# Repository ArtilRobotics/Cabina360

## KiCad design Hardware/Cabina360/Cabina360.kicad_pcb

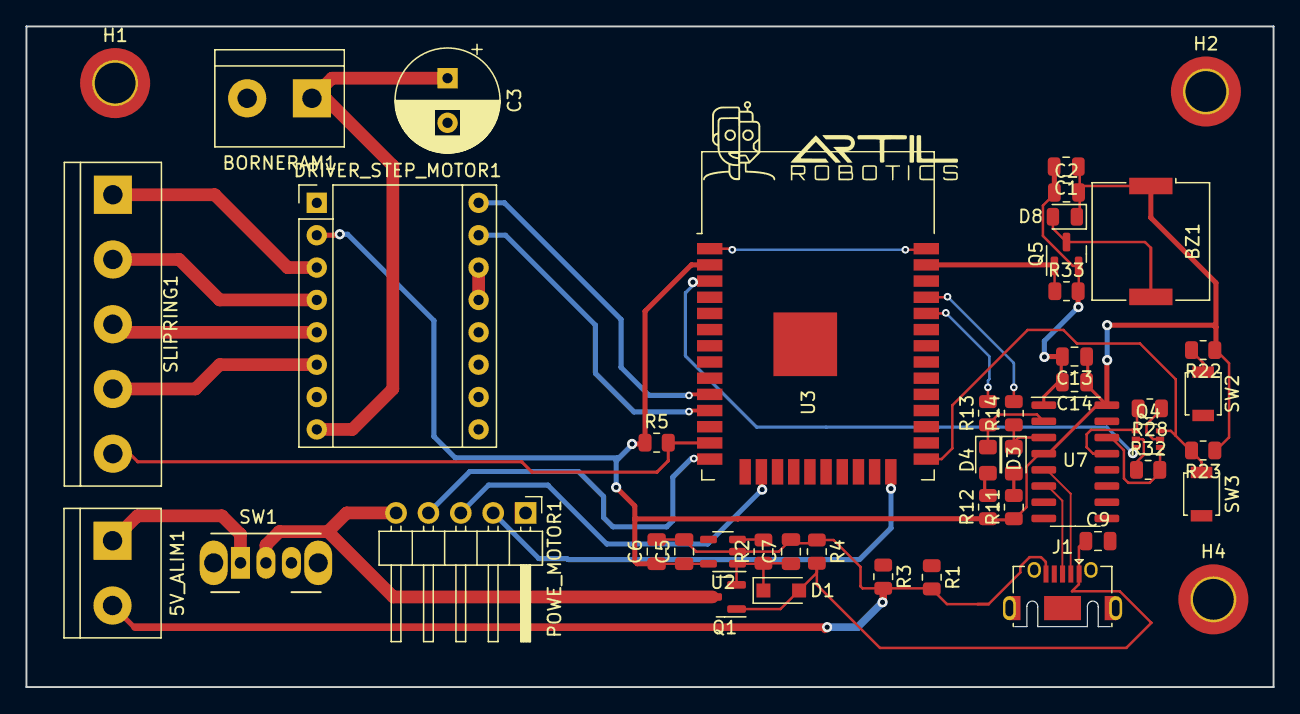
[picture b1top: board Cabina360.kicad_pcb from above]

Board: 2 copper layers, 97.9 x 51.8 mm, 46 parts (0 on the bottom side), 34 nets.

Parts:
5V_ALIM1: 5V GND; TerminalBlock_bornier-2_P5.08mm
BORNERAM1: MOTOR+ MOTOR-; TerminalBlock_bornier-2_P5.08mm
BZ1: Buzzer; Buzzer_Murata_PKMCS0909E
C1, C6, C7, C9, C13: 10uF; C_0805_2012Metric
C2: 0.1uF; C_0805_2012Metric
C3: 10uF; CP_Radial_D8.0mm_P3.50mm
C5: 1uF; C_0805_2012Metric
C14: 10nF; C_0805_2012Metric
D1: MBR1020VL; D_SOD-123F
D3, D4: LED; LED_0805_2012Metric_Pad1.15x1.40mm_HandSolder
D8: 1N4151; D_0805_2012Metric
DRIVER_STEP_MOTOR1: Pololu_Breakout_A4988; Pololu_Breakout-16_15.2x20.3mm
H1, H2, H4: MountingHole; MountingHole_3.2mm_M3_ISO14580_Pad_TopBottom
J1: USB_C_Receptacle_USB2.0; USB_Micro-AB_Molex_47590-0001
POWE_MOTOR1: PINES; PinHeader_1x05_P2.54mm_Horizontal
Q1: DMG2301L; SOT-23
Q4: MBT3904DW1; SOT-363_SC-70-6
Q5: DMG3406L; SOT-23
R1, R3: 5.1K; R_0805_2012Metric
R2, R5, R22, R23: 10K; R_0805_2012Metric
R4, R33: 100K; R_0805_2012Metric
R11, R12, R28, R32: 1K; R_0805_2012Metric
R13, R14: 100; R_0805_2012Metric
SLIPRING1: PINES; TerminalBlock_bornier-5_P5.08mm
SW1: SW_DPDT_x2; SW_CuK_OS102011MA1QN1_SPDT_Angled
SW2: Reset; SW_SPST_B3U-1000P
SW3: Boot; SW_SPST_B3U-1000P
U2: AP2112K-3.3; SOT-23-5
U3: ESP32-WROOM-32
U7: CH340C; SOIC-16_3.9x9.9mm_P1.27mm

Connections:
+3V3: BZ1.1 (-), C1.1, C2.2, C5.1, C6.1, C13.1, C14.1, D8.1 (K), DRIVER_STEP_MOTOR1.2 (VDD), R5.1, R11.1, R12.1, R22.1, R23.1, U2.5 (VOUT), U3.2 (VDD), U7.4 (V3), U7.16 (VCC)
+BATT: POWE_MOTOR1.5, Q1.3 (D), SW1.2 (B)
/Buzzer: Q5.1 (G), R33.1, U3.37 (IO23)
/DIR: DRIVER_STEP_MOTOR1.16 (DIR), U3.10 (IO25)
/F_CARRERA: R5.2, SLIPRING1.5, U3.13 (IO14)
/LPWM: POWE_MOTOR1.3, U3.16 (IO13)
/PWM: POWE_MOTOR1.4, U3.14 (IO12)
/RPWM: POWE_MOTOR1.2, U3.24 (IO2)
/Reset: R22.2, SW2.2
/STEP: DRIVER_STEP_MOTOR1.15 (STEP), U3.11 (IO26)
/VMOT: BORNERAM1.1, C3.1, DRIVER_STEP_MOTOR1.8 (VMOT)
Boot: Q4.3 (C2), R23.2, SW3.2, U3.25 (IO0)
DTR: Q4.4 (E2), R28.2, U7.13 (~DTR)
EN: Q4.6 (C1), U3.3 (EN)
GND: 5V_ALIM1.2, BORNERAM1.2, C1.2, C2.1, C3.2, C5.2, C6.2, C7.2, C9.2, C13.2, C14.2, DRIVER_STEP_MOTOR1.1 (GND), DRIVER_STEP_MOTOR1.7 (GND), POWE_MOTOR1.1, Q5.2 (S), R1.2, R3.2, R4.1, R33.2, SW2.1, SW3.1, U2.2 (GND), U3.1 (GND), U3.15 (GND), U3.38 (GND), U3.39 (GND), U7.1 (GND)
unnamed: BZ1.2 (+), D8.2 (A), Q5.3 (D)
unnamed: C7.1, D1.1 (K), Q1.2 (S), R2.1, U2.1 (VIN)
unnamed: D3.1 (K), R14.1, U7.3 (RXD)
unnamed: D3.2 (A), R11.2
unnamed: D4.1 (K), R13.1, U7.2 (TXD)
unnamed: D4.2 (A), R12.2
unnamed: DRIVER_STEP_MOTOR1.3 (1B), SLIPRING1.1
unnamed: DRIVER_STEP_MOTOR1.4 (1A), SLIPRING1.2
unnamed: DRIVER_STEP_MOTOR1.5 (2A), SLIPRING1.3
unnamed: DRIVER_STEP_MOTOR1.6 (2B), SLIPRING1.4
unnamed: DRIVER_STEP_MOTOR1.13 (~RESET), DRIVER_STEP_MOTOR1.14 (~SLEEP)
unnamed: Q4.2 (B1), R28.1
unnamed: Q4.5 (B2), R32.1
unnamed: R2.2, U2.3 (EN)
unnamed: 5V_ALIM1.1, SW1.1 (A)
RTS: Q4.1 (E1), R32.2, U7.14 (~RTS)
RXD: R14.2, U3.35 (TXD0/IO1)
TXD: R13.2, U3.34 (RXD0/IO3)
VBUS: C9.1, D1.2 (A), Q1.1 (G), R4.2

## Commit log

2022-12-27 Agrege archivos base para PCB
2023-01-09 feat!: Estructura de escenas base para la app movil y grabacion de video y almacenamiento en galeria
2023-01-10 feat: Agrege un timer cuando el usuario presiona grabar
2023-01-10 feat: Se eliminaron los scripts relacionados a la captura de video
2023-02-27 ft!: Actualización Sistema Electronico
2023-03-13 feat! Added CAD from Workbrench
